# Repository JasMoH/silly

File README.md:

# silly
silly boards and other art

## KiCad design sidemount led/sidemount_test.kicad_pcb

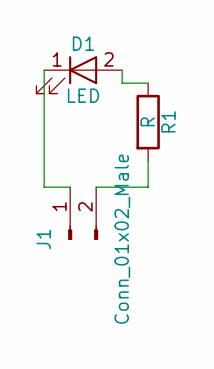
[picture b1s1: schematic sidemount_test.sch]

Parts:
D1: LED; 1206_bottom_mount_sideways
J1: Conn_01x02_Male; Pin_Header_Straight_1x02_Pitch2.54mm
R1: R; R_0805_HandSoldering

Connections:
unnamed: D1.1 (K), J1.1
unnamed: D1.2 (A), R1.1
unnamed: J1.2, R1.2

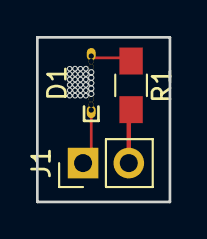
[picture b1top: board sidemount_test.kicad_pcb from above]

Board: 2 copper layers, 7.4 x 9.1 mm, 3 parts (0 on the bottom side), 3 nets.

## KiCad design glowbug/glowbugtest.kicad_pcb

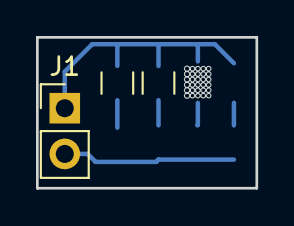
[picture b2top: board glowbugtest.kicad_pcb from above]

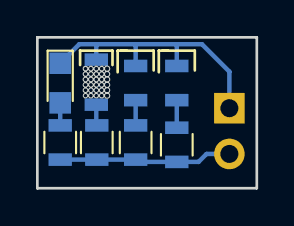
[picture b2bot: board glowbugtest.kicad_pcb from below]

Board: 2 copper layers, 12.2 x 8.4 mm, 9 parts (5 on the bottom side), 6 nets.

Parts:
D1: LED; GlowBug_CircleRelief
D2: LED; GlowBug_CircleRelief_Single_Side
D3: LED; GlowBug_Holes
D4: LED; LED_0805
J1: Conn_01x02; Pin_Header_Straight_1x02_Pitch2.54mm
R1, R2, R3, R4: 200; R_0805

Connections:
unnamed: D1.1, D2.1, D3.1, D4.1, J1.1
unnamed: D1.2, R1.1
unnamed: D2.2, R2.1
unnamed: D3.2, R3.1
unnamed: D4.2, R4.1
unnamed: J1.2, R1.2, R2.2, R3.2, R4.2

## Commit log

2018-01-04 initial commit
    many of these were already up
2018-01-06 initial scan
2018-01-06 digital ink, layer separation
2018-01-06 fish component creation
2018-01-06 added solder mask reliefe for visual copper elements
2018-01-06 created first pass anglerfish pcb
2018-01-06 added power supply pads
2018-01-06 initial commit of extant nfiles
2018-01-06 changed to circle reliefed led
2018-02-05 updated bottom pad
